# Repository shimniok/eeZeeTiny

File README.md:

# eeZeeTiny

A breadboard development board for 8-pin ATtiny (13, 85, etc.) including AVR ISP header, reset switch and pull-up resistor, and bypass caps. Perfect for low power projects, dedicated tasks, Internet of Things, and so much more.

[eeZeeTiny User Guide](documentation/)

[Buy now on Tindie](https://www.tindie.com/products/bot_thoughts/eezee-tiny-breakout-programming-board-kit/).

Features
* It doesn't get any smaller than this!
* Designed for breadboarding: all pins exposed, all support circuits included
* Includes AVR ISP header for in-circuit programming
* 0.1uF and 10uF filtering capacitors installed underneath
* Reset switch and pull-up resistor included
* Works with ATtiny11, ATtiny12, ATtiny13, ATtiny25, ATtiny45, ATtiny85
* Program ATtinyX5 with Arduino IDE

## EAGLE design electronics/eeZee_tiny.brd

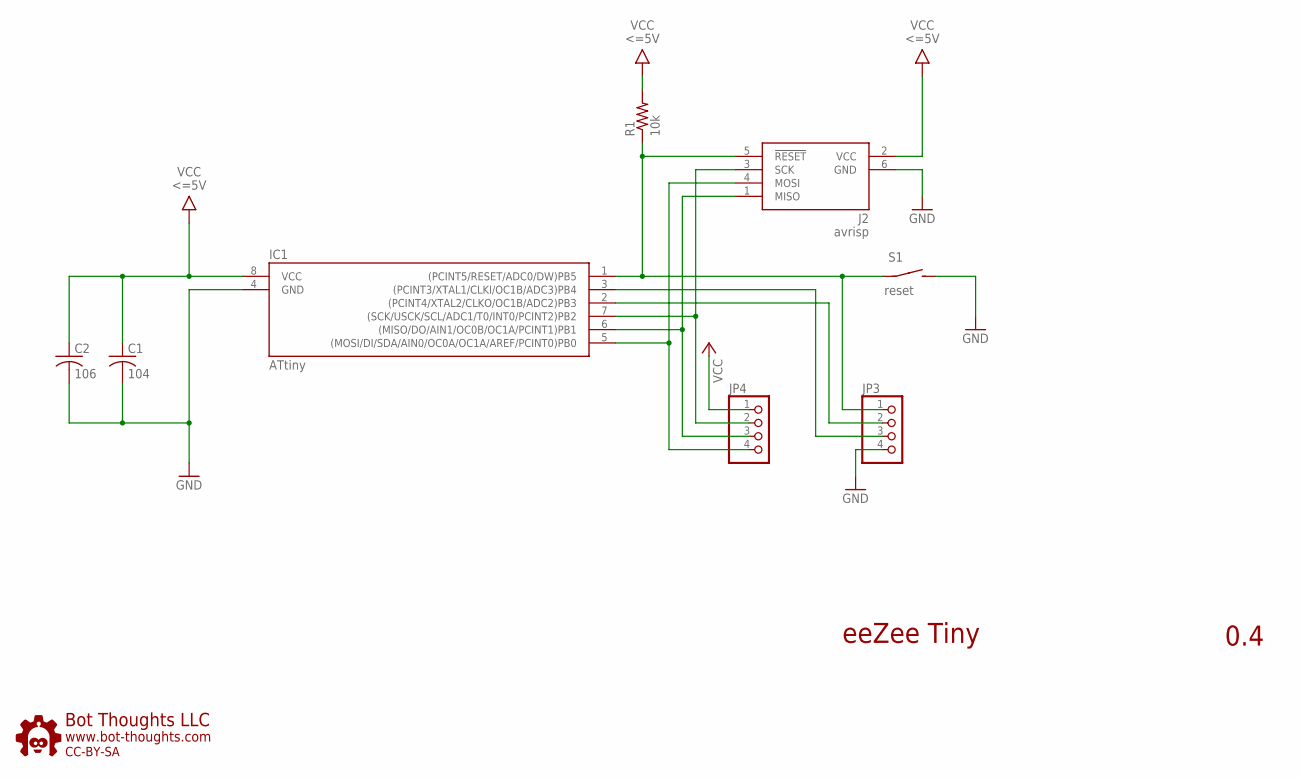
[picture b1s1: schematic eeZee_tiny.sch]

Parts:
C1: 104; C0603; PARTNO 0603YC104KAT2A
C2: 106; C1206; PARTNO F930J107MBA
IC1: ATtiny; DIL08
J2: avrisp; CON6P2R
JP3, JP4: PINHD-1X04_2.54-S; 1X04-S
R1: 10k; R0603; PARTNO ERJ-3GEYJ103V
S1: reset; 6MMTACTILE_RECT
U$1: BTLOGO-LOGO-MD; BTLOGOM

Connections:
!RESET: IC1.1 ((PCINT5/RESET/ADC0/DW)PB5), J2.5 (!RESET), JP3.1, R1.1, S1.P$1
GND: C1.2, C2.2, IC1.4 (GND), J2.6 (GND), JP3.4, S1.P$2 (S)
MISO: IC1.6 ((MISO/DO/AIN1/OC0B/OC1A/PCINT1)PB1), J2.1 (MISO), JP4.3
MOSI: IC1.5 ((MOSI/DI/SDA/AIN0/OC0A/OC1A/AREF/PCINT0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), J2.4 (MOSI), JP4.4
PB3: IC1.2 ((PCINT4/XTAL2/CLKO/OC1B/ADC2)PB3), JP3.2
PB4: IC1.3 ((PCINT3/XTAL1/CLKI/OC1B/ADC3)PB4), JP3.3
SCK: IC1.7 ((SCK/USCK/SCL/ADC1/T0/INT0/PCINT2)PB2), J2.3 (SCK), JP4.2
VCC: C1.1, C2.1, IC1.8 (VCC), J2.2 (VCC), JP4.1, R1.2

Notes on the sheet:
eeZee Tiny
0.4

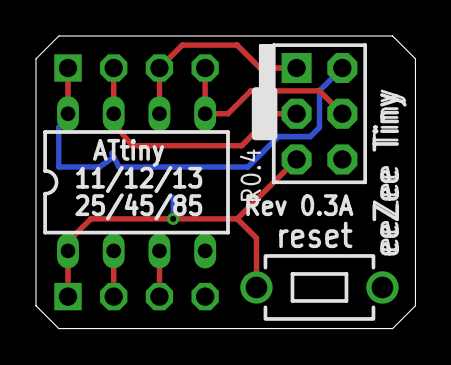
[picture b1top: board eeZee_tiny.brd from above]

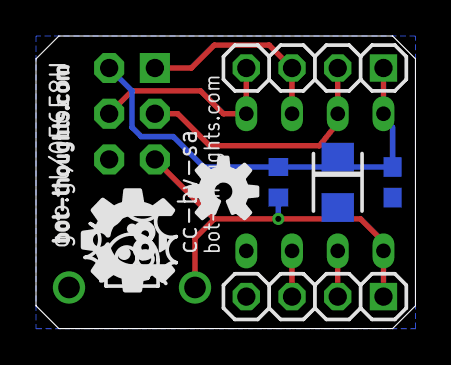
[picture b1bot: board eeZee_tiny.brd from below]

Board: 2 copper layers, 21.1 x 16.3 mm, 9 parts (6 on the bottom side), 8 nets.

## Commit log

2012-11-22 Initial revision
2013-01-08 Moved caps, mods to routing, added logos, added SCK indicator mark
2013-01-31 Revised layout to reduce leading edge and side edge clearances for better breadboarding.
2013-02-12 Revised board layout removing leading edge, using 6x3mm switch and making board narrower. Revised 8-pin tiny pad thickness minimum. Moved reset resistor for easier assembly. Revised and relocated log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
2013-08-06 Rev 0.2, shrunk board, mitered corners, added polarity silk to tantalum.
2014-03-29 Created ATtiny13 serial demo, created subdir for blinky light demo
2014-03-31 Converted project to AVR Studio 4, sick of trying to learn gcc assembly when examples are so scarce :)
2014-10-17 Updated DRC with 10mil/8mil spacing, 10mil distances.
2015-05-04 Revised license files
2015-07-30 Added assembly guides
2015-07-31 Renamed assembly guide
2015-08-06 Moved firmware to examples
2016-12-08 revised 8pdip pads, rerouted avrisp traces, changed passives layout, changed main cap from 100u to 10u and changed to 1206 pkg, replaced attiny13 with attiny25 from bt library, changed avrisp to vers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
2016-12-08 updated gerbers
2016-12-08 removed dri file
2017-03-07 added larson example for gcc toolchain / avrdude
2017-03-07 added extensions for avr-gcc
2017-06-07 Updated makefile to build for either t13 or t85
2017-06-13 converted for avrispv2 / pololu
2017-06-14 fixed bug in makefile, remake for each build, include for install
2017-06-14 fixed formatting
2017-06-14 added usbasp
2017-06-27 added assembly instructions in markdown
2017-06-27 added arduino instructions
2017-06-27 added avr-gcc instructions
2017-06-27 added hardwre programmer instructions
2017-06-27 added docs readme, linked to docs from main readme
2017-06-27 added main docs pic plus pinout pic
2017-06-27 moved Blinky into Atmel studio subdir
2017-06-27 moved larson to avr-gcc example subdir
2017-06-27 moved T13serial to studio example subdir
2017-06-27 added arduino example
2017-06-27 added zip
2017-06-27 added target save file
2017-06-27 tweak makefile to fix issue
2017-06-27 removed odt / pdf files
2017-06-27 added avrisp image
2017-06-27 added atmel studio docs
2017-06-27 removed eezeetiny841 stuff, added comment about examples with avrdude
2017-06-27 shrunk image sizes

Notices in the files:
electronics/eeZee_tiny.brd:
cc-by-sa
